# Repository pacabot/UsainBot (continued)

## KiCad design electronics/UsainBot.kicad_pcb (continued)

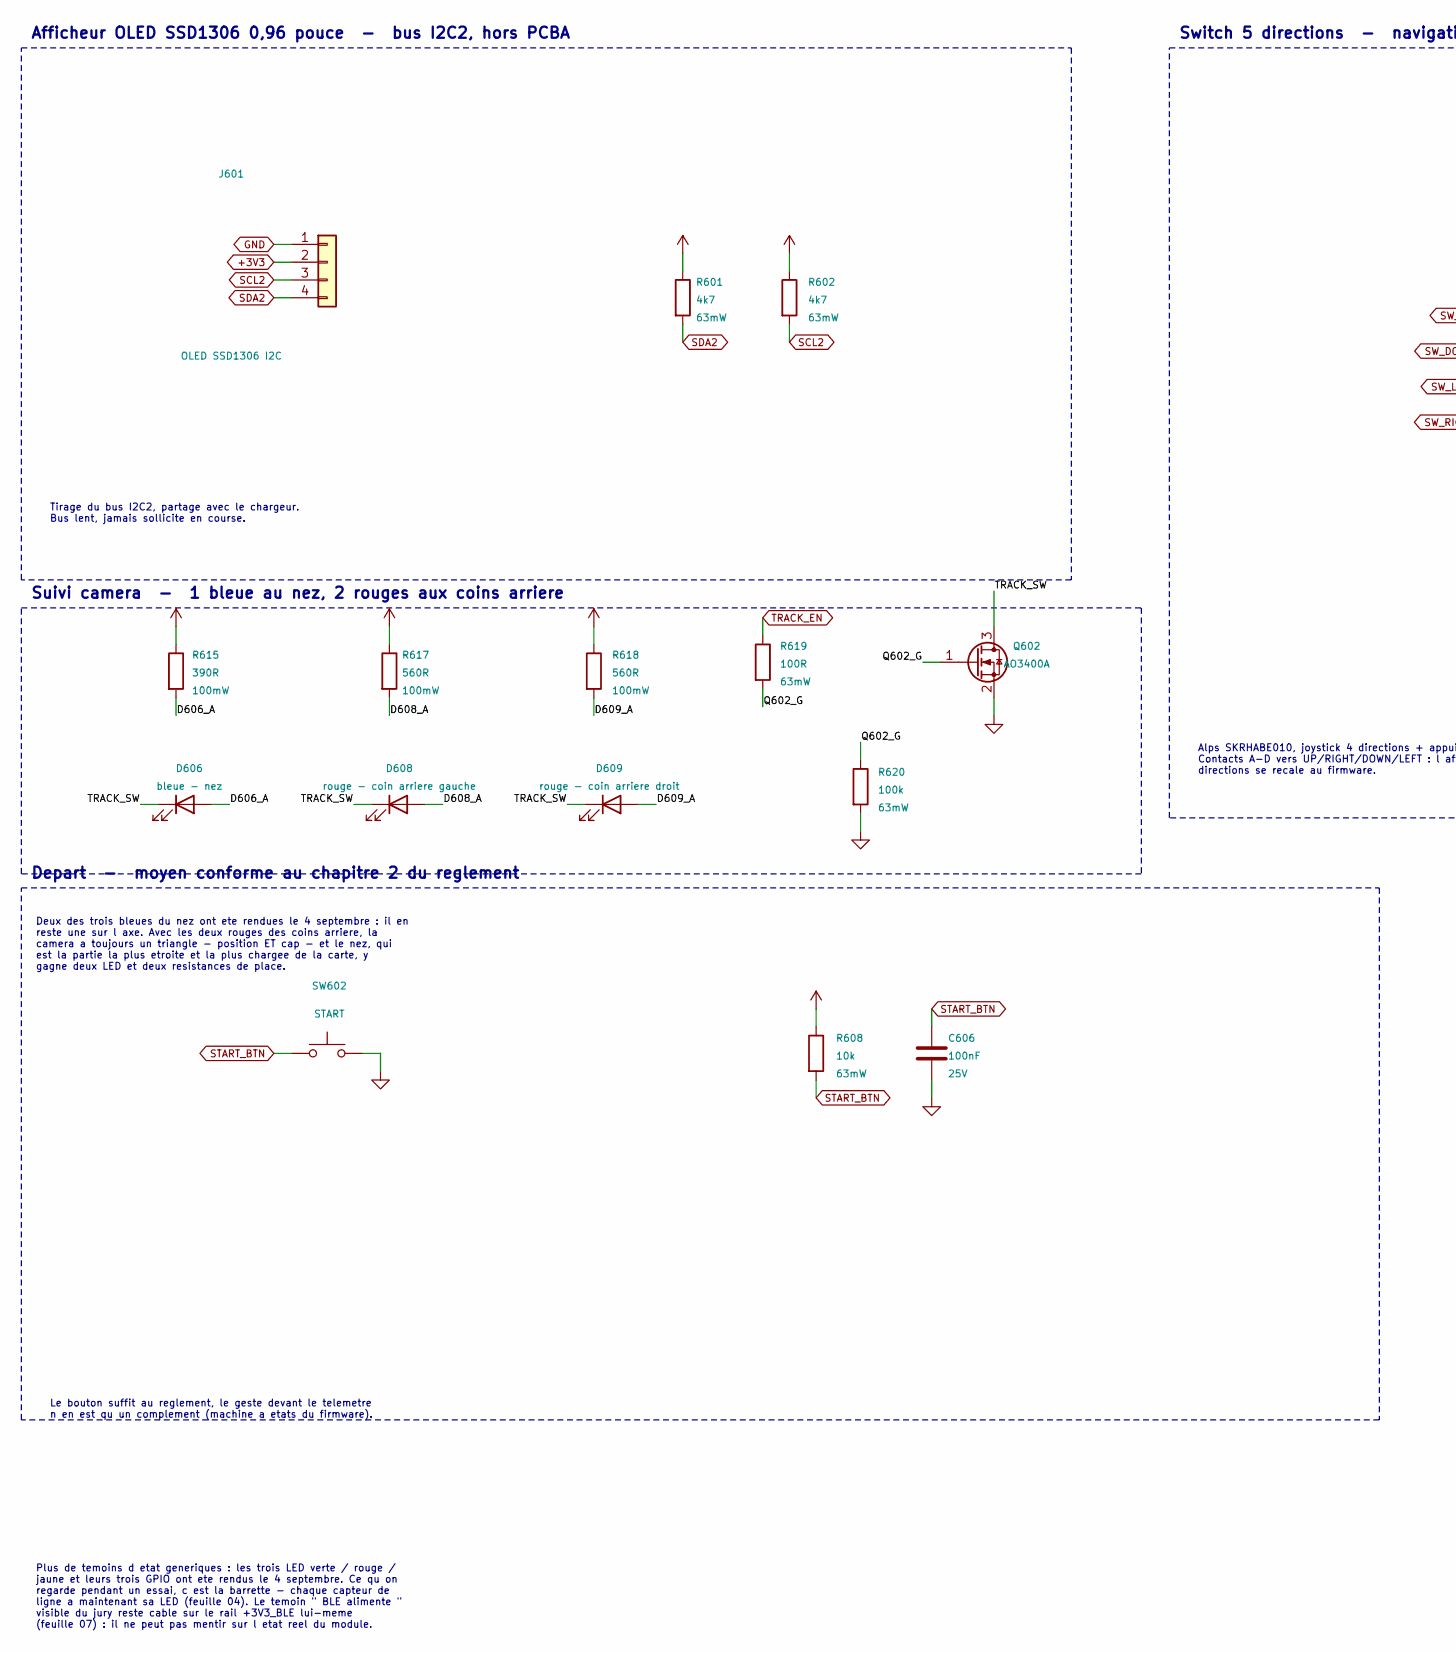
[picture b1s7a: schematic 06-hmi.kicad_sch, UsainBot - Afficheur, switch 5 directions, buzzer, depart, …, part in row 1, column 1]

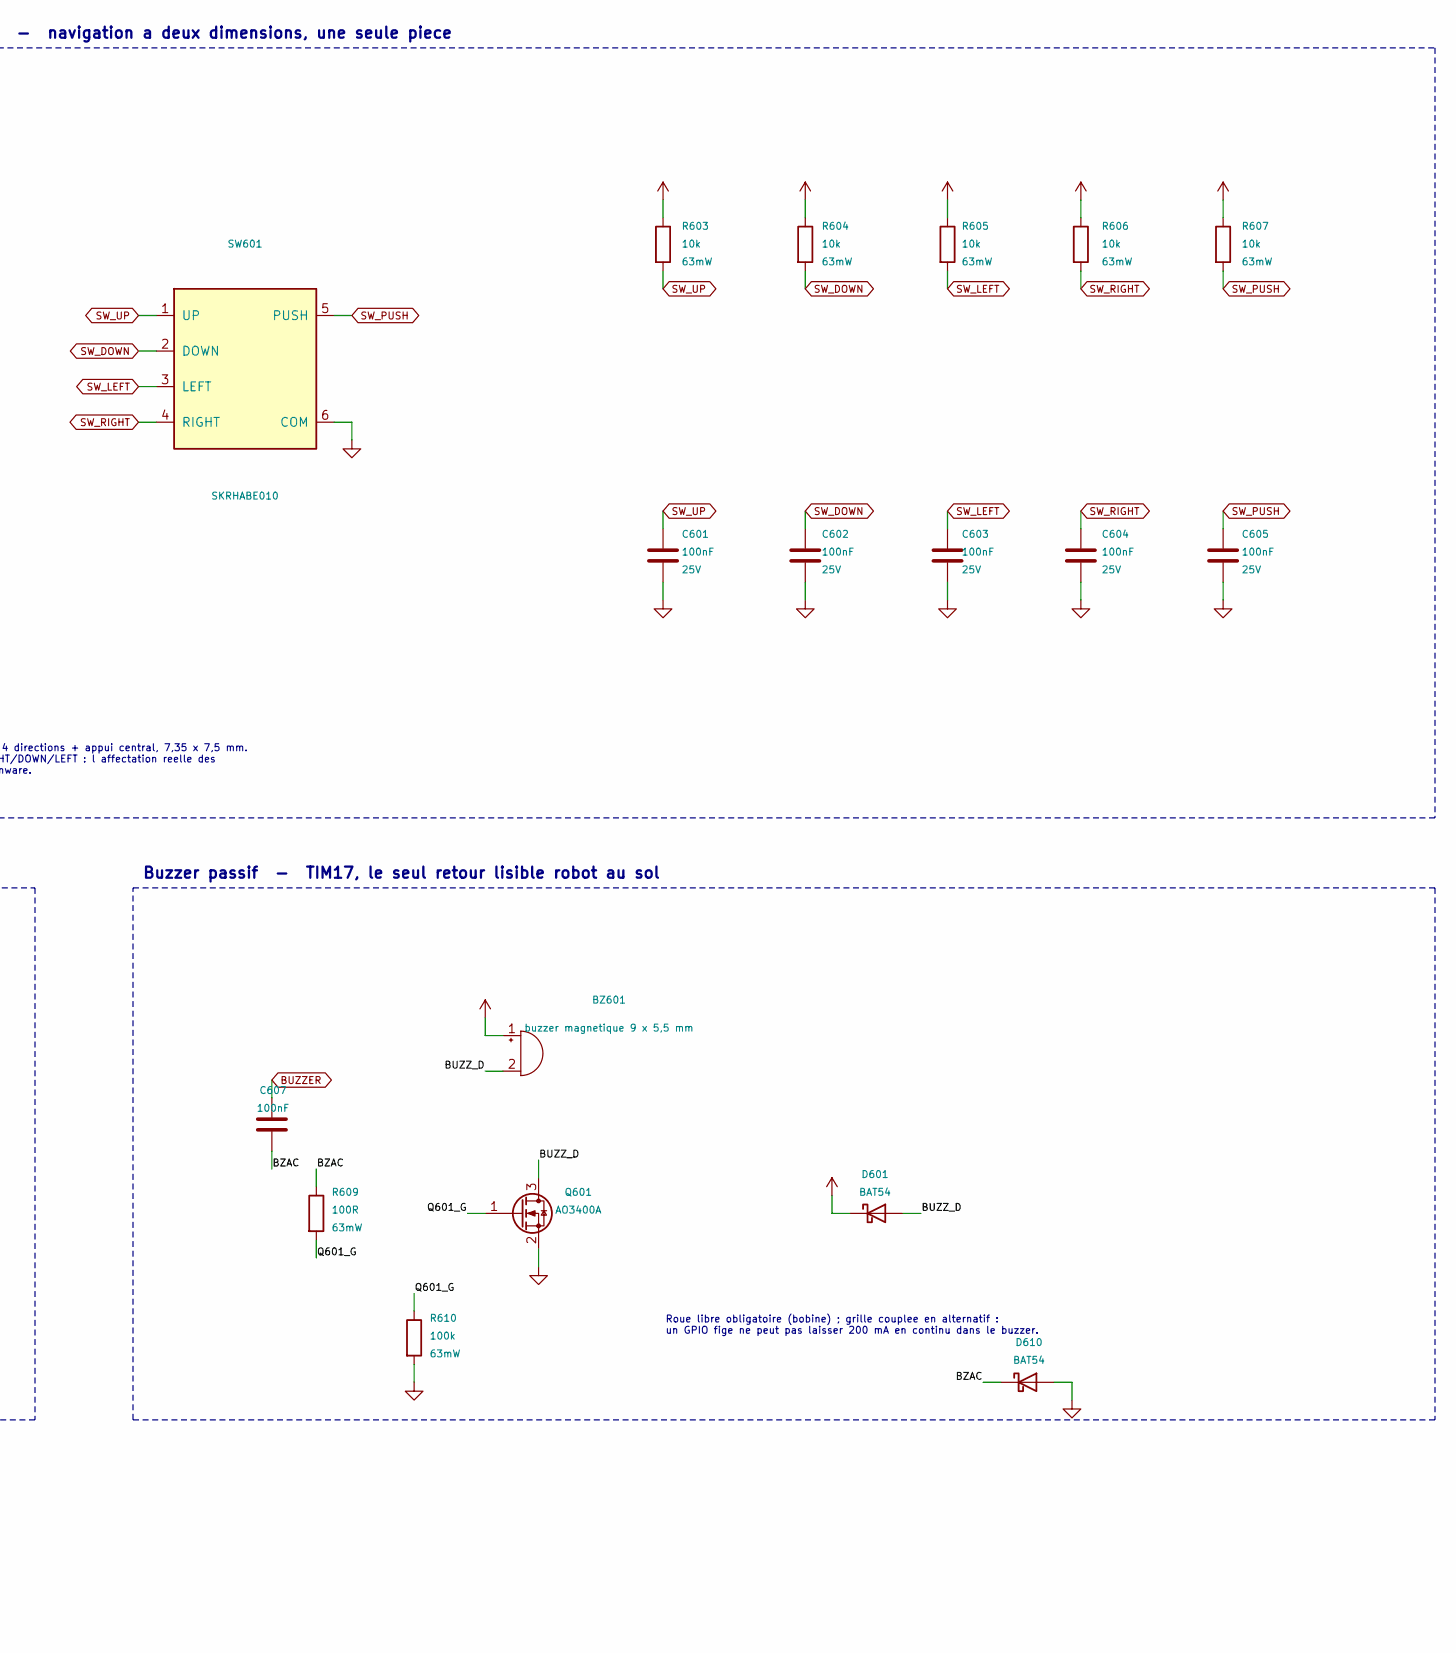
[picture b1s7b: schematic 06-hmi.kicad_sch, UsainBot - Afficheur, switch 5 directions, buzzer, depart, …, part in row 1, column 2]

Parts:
BZ601: buzzer magnetique 9 x 5,5 mm; MagneticBuzzer_ProSignal_ABI-009-RC
C601, C602, C603, C604, C605, C606: 100nF; C_0402_1005Metric; Voltage 25V
C607: 100nF; C_0402_1005Metric
D601, D610: BAT54; D_SOD-323
D606: bleue - nez; LED_0603_1608Metric
D608: rouge - coin arriere gauche; LED_0603_1608Metric
D609: rouge - coin arriere droit; LED_0603_1608Metric
J601: OLED SSD1306 I2C; OLED_096_I2C
Q601, Q602: AO3400A; SOT-23
R601, R602: 4k7; R_0402_1005Metric
R603, R604, R605, R606, R607, R608: 10k; R_0402_1005Metric
R609, R619: 100R; R_0402_1005Metric
R610, R620: 100k; R_0402_1005Metric
R615: 390R; R_0603_1608Metric
R617, R618: 560R; R_0603_1608Metric
SW601: SKRHABE010; LCSC C144855
SW602: START; SW_SPST_B3U-1000P

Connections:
/IHM/BUZZ_D: BZ601.2 (-), D601.2 (A), Q601.3 (D)
/IHM/BZAC: C607.2, D610.1 (K), R609.1
/IHM/D606_A: D606.2 (A), R615.2
/IHM/D608_A: D608.2 (A), R617.2
/IHM/D609_A: D609.2 (A), R618.2
/IHM/Q601_G: Q601.1 (G), R609.2, R610.1
/IHM/Q602_G: Q602.1 (G), R619.2, R620.1
/IHM/TRACK_SW: D606.1 (K), D608.1 (K), D609.1 (K), Q602.3 (D)
BUZZER: C607.1; also elsewhere on the board
SCL2: J601.3, R602.2; also elsewhere on the board
SDA2: J601.4, R601.2; also elsewhere on the board
START_BTN: C606.1, R608.2, SW602.1; also elsewhere on the board
SW_DOWN: C602.1, R604.2, SW601.2 (DOWN); also elsewhere on the board
SW_LEFT: C603.1, R605.2, SW601.3 (LEFT); also elsewhere on the board
SW_PUSH: C605.1, R607.2, SW601.5 (PUSH); also elsewhere on the board
SW_RIGHT: C604.1, R606.2, SW601.4 (RIGHT); also elsewhere on the board
SW_UP: C601.1, R603.2, SW601.1 (UP); also elsewhere on the board
TRACK_EN: R619.1; also elsewhere on the board

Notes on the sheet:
Plus de temoins d etat generiques : les trois LED verte / rouge / jaune et leurs trois GPIO ont ete rendus le 4 septembre. Ce qu on regarde pendant un essai, c est la barrette - chaque capteur de ligne a maintenant sa LED (feuille 04). Le temoin " BLE alimente " visible du jury reste cable sur le r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
Deux des trois bleues du nez ont ete rendues le 4 septembre : il en reste une sur l axe. Avec les deux rouges des coins arriere, la camera a toujours un triangle - position ET cap - et le nez, qui est la partie la plus etroite et la plus chargee de la carte, y gagne deux LED et deux resistances de 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
Le bouton suffit au reglement, le geste devant le telemetre n en est qu un complement (machine a etats du firmware).
Tirage du bus I2C2, partage avec le chargeur. Bus lent, jamais sollicite en course.
Switch 5 directions - navigation a deux dimensions, une seule piece
Buzzer passif - TIM17, le seul retour lisible robot au sol
Suivi camera - 1 bleue au nez, 2 rouges aux coins arriere
Roue libre obligatoire (bobine) ; grille couplee en alternatif : un GPIO fige ne peut pas laisser 200 mA en continu dans le buzzer.
Depart - moyen conforme au chapitre 2 du reglement
Afficheur OLED SSD1306 0,96 pouce - bus I2C2, hors PCBA
Alps SKRHABE010, joystick 4 directions + appui central, 7,35 x 7,5 mm. Contacts A-D vers UP/RIGHT/DOWN/LEFT : l affectation reelle des directions se recale au firmware.

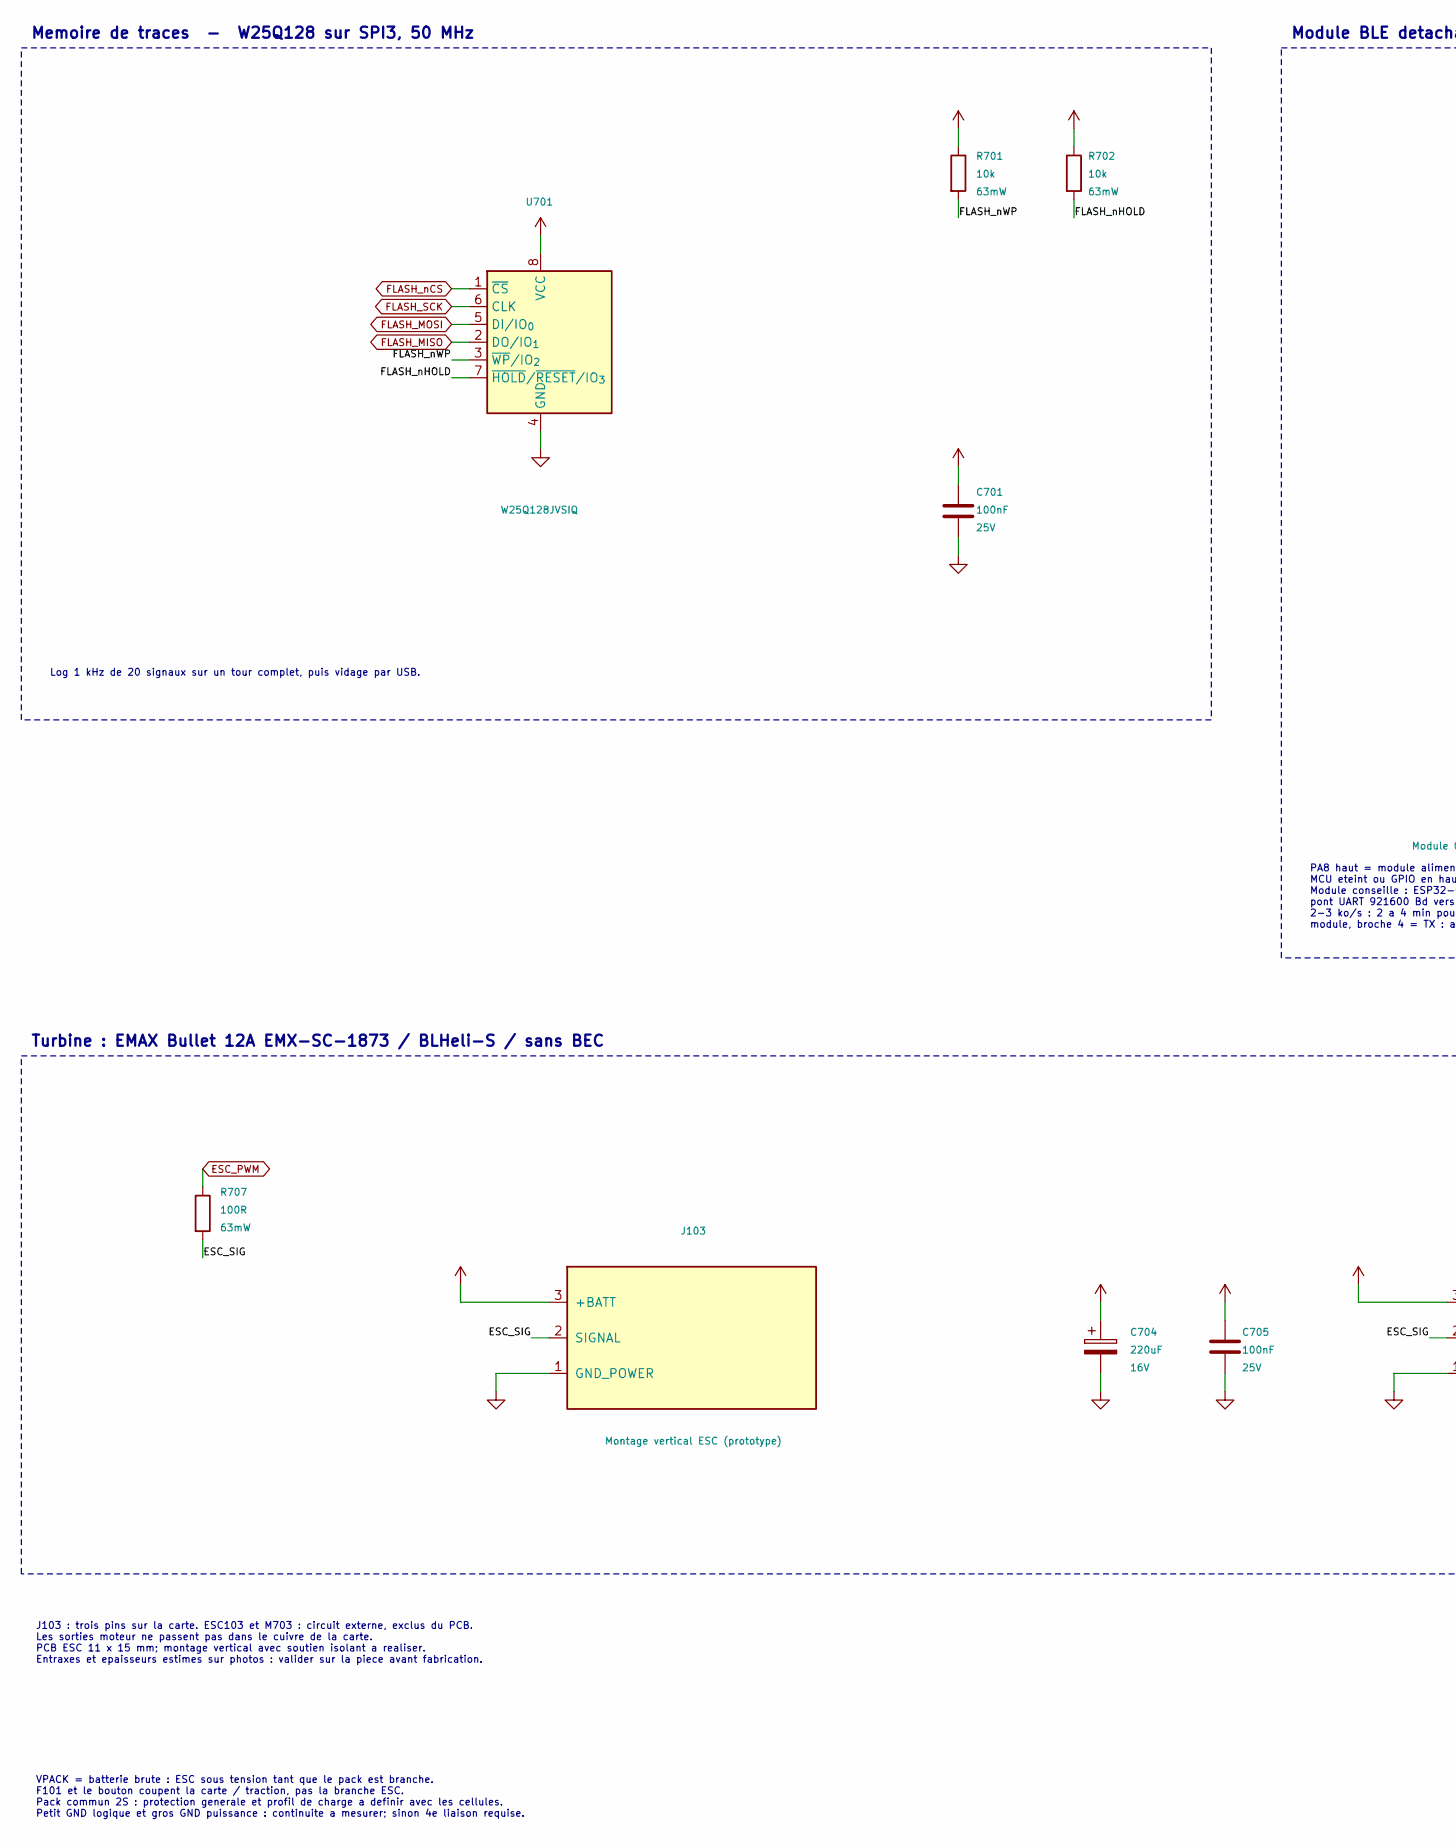
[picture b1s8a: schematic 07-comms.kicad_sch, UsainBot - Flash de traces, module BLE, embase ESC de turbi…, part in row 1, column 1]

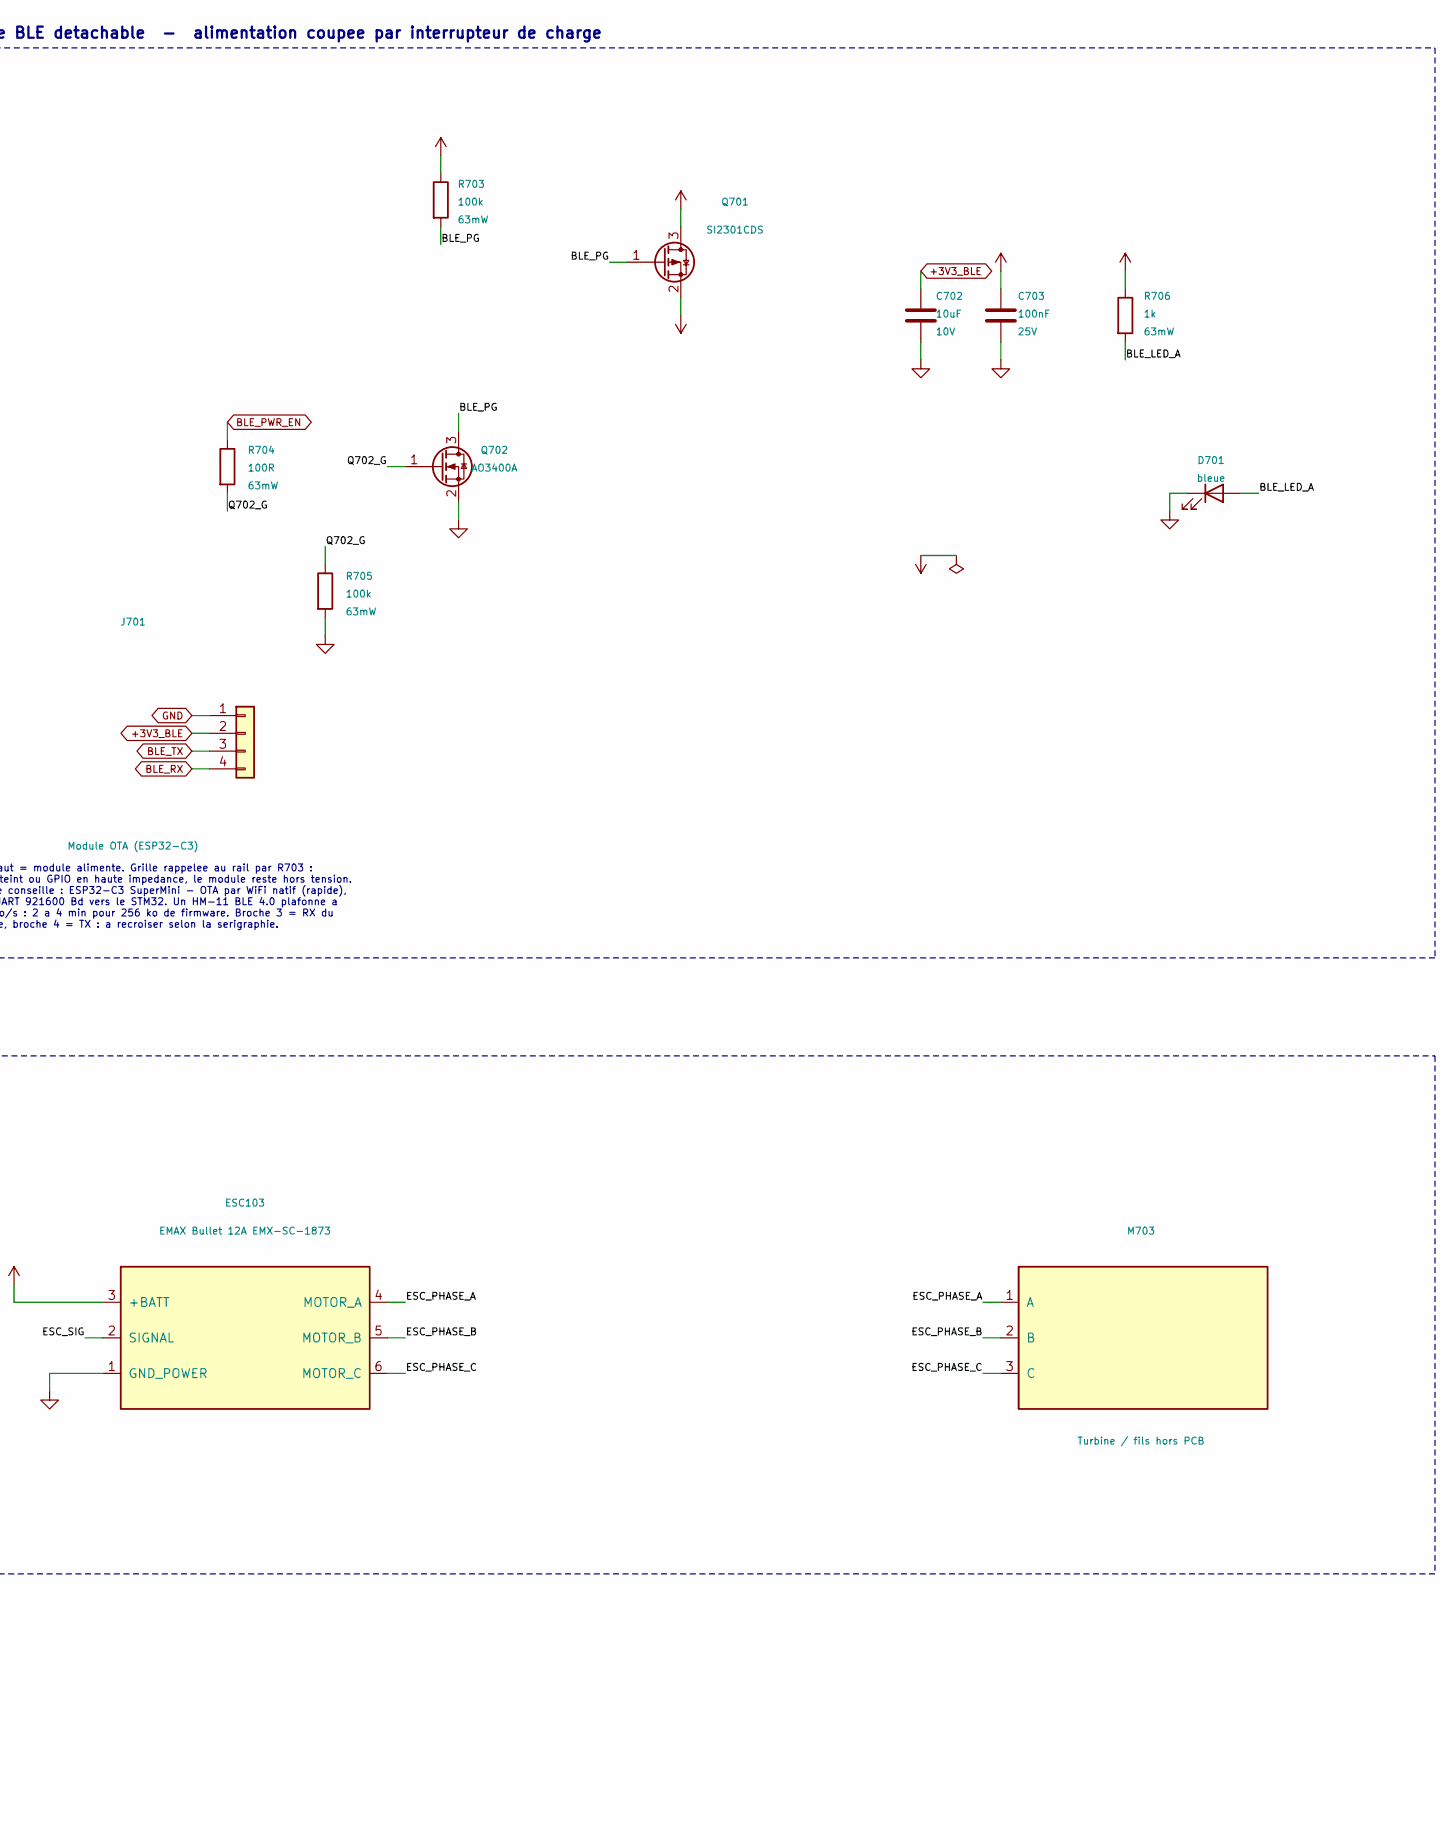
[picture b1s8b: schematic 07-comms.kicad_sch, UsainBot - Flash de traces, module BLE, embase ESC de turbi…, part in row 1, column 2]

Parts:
C701, C703, C705: 100nF; C_0402_1005Metric; Voltage 25V
C702: 10uF; C_0805_2012Metric; Voltage 10V
C704: 220uF; CP_Elec_6.3x7.7; Voltage 16V
D701: bleue; LED_0603_1608Metric
ESC103: EMAX Bullet 12A EMX-SC-1873; EMAX_Bullet_12A_Vertical_3Pin_PROTOTYPE; MPN EMX-SC-1873
J103: Montage vertical ESC (prototype); EMAX_Bullet_12A_Vertical_3Pin_PROTOTYPE
J701: Module OTA (ESP32-C3); PinHeader_1x04_P2.54mm_Vertical
M703: Turbine / fils hors PCB
Q701: SI2301CDS; SOT-23
Q702: AO3400A; SOT-23
R701, R702: 10k; R_0402_1005Metric
R703, R705: 100k; R_0402_1005Metric
R704, R707: 100R; R_0402_1005Metric
R706: 1k; R_0402_1005Metric
U701: W25Q128JVSIQ; SOIC-8_5.3x5.3mm_P1.27mm

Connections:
+3V3_BLE: C702.1, C703.1, J701.2, Q701.3 (D), R706.1
/Traces et turbine/BLE_LED_A: D701.2 (A), R706.2
/Traces et turbine/BLE_PG: Q701.1 (G), Q702.3 (D), R703.2
/Traces et turbine/ESC_SIG: ESC103.2 (SIGNAL), J103.2 (SIGNAL), R707.2
/Traces et turbine/FLASH_nHOLD: R702.2, U701.7 (~HOLD/~RESET/IO_{3})
/Traces et turbine/FLASH_nWP: R701.2, U701.3 (~WP/IO_{2})
/Traces et turbine/Q702_G: Q702.1 (G), R704.2, R705.1
BLE_PWR_EN: R704.1; also elsewhere on the board
BLE_RX: J701.4; also elsewhere on the board
BLE_TX: J701.3; also elsewhere on the board
ESC_PWM: R707.1; also elsewhere on the board
FLASH_MISO: U701.2 (DO/IO_{1}); also elsewhere on the board
FLASH_MOSI: U701.5 (DI/IO_{0}); also elsewhere on the board
FLASH_SCK: U701.6 (CLK); also elsewhere on the board
FLASH_nCS: U701.1 (~CS); also elsewhere on the board
unnamed: ESC103.4 (MOTOR_A), M703.1 (A)
unnamed: ESC103.5 (MOTOR_B), M703.2 (B)
unnamed: ESC103.6 (MOTOR_C), M703.3 (C)
VPACK: C704.1, C705.1, ESC103.3 (+BATT), J103.3 (+BATT); also elsewhere on the board

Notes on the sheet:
Memoire de traces - W25Q128 sur SPI3, 50 MHz
Turbine : EMAX Bullet 12A EMX-SC-1873 / BLHeli-S / sans BEC
Log 1 kHz de 20 signaux sur un tour complet, puis vidage par USB.
PA8 haut = module alimente. Grille rappelee au rail par R703 : MCU eteint ou GPIO en haute impedance, le module reste hors tension. Module conseille : ESP32-C3 SuperMini - OTA par WiFi natif (rapide), pont UART 921600 Bd vers le STM32. Un HM-11 BLE 4.0 plafonne a 2-3 ko/s : 2 a 4 min pour 256 ko de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
VPACK = batterie brute : ESC sous tension tant que le pack est branche. F101 et le bouton coupent la carte / traction, pas la branche ESC. Pack commun 2S : protection generale et profil de charge a definir avec les cellules. Petit GND logique et gros GND puissance : continuite a mesurer; sinon 4e l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
J103 : trois pins sur la carte. ESC103 et M703 : circuit externe, exclus du PCB. Les sorties moteur ne passent pas dans le cuivre de la carte. PCB ESC 11 x 15 mm; montage vertical avec soutien isolant a realiser. Entraxes et epaisseurs estimes sur photos : valider sur la piece avant fabrication.
Module BLE detachable - alimentation coupee par interrupteur de charge

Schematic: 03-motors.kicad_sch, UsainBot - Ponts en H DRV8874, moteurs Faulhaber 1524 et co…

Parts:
C301, C303, C305, C351, C353, C355: 100nF; C_0402_1005Metric; Voltage 25V
C302, C308, C309, C352, C358, C359: 1nF; C_0402_1005Metric; Voltage 25V
C304, C354: 100uF; CP_EIA-7343-20_Kemet-V; Voltage 16V poly
C306, C356: 22nF; C_0402_1005Metric; Voltage 25V
C307, C357: 100nF; C_0805_2012Metric; Voltage 50V
C310: 1uF; C_0402_1005Metric; Voltage 25V; LCSC C52923
C311: 4.7uF; C_0603_1608Metric; Voltage 16V; LCSC C19666
J301, J351: Moteur Faulhaber + IE2; TE_Micro-MaTch_215079-6_2x03_P1.27mm_Vertical; MPN TE 7-215079-6
R301, R304, R306, R354, R356: 10k; R_0402_1005Metric
R302: 6k8; R_0402_1005Metric
R303, R353: 100k; R_0402_1005Metric
R305, R355: 20k; R_0402_1005Metric
R307, R357: 1k; R_0402_1005Metric
R308, R309, R310, R358, R359, R360: 100R; R_0402_1005Metric
U301, U351: DRV8874PWPR; HTSSOP-16-1EP_4.4x5mm_P0.65mm_EP3.4x5mm; LCSC C1855818
U302: TPS70950DBVR; SOT-23-5; LCSC C96028

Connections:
/Moteurs/CPH_L: C306.1, U301.13 (CPH)
/Moteurs/CPH_R: C356.1, U351.13 (CPH)
/Moteurs/CPL_L: C306.2, U301.14 (CPL)
/Moteurs/CPL_R: C356.2, U351.14 (CPL)
/Moteurs/ENC_5V: C311.1, J301.4 (VDD), J351.4 (VDD), U302.5 (OUT)
/Moteurs/ENC_L_A_RAW: J301.6 (A), R309.1
/Moteurs/ENC_L_B_RAW: J301.5 (B), R310.1
/Moteurs/ENC_R_A_RAW: J351.6 (A), R359.1
/Moteurs/ENC_R_B_RAW: J351.5 (B), R360.1
/Moteurs/IMODE_L: R305.1, U301.7 (IMODE)
/Moteurs/IMODE_R: R355.1, U351.7 (IMODE)
/Moteurs/IPROPI_L_RAW: R307.1, R308.1, U301.6 (IPROPI)
/Moteurs/IPROPI_R_RAW: R357.1, R358.1, U351.6 (IPROPI)
/Moteurs/MOT_L_OUT1: C307.1, J301.2 (M+), U301.8 (OUT1)
/Moteurs/MOT_L_OUT2: C307.2, J301.1 (M-), U301.10 (OUT2)
/Moteurs/MOT_R_OUT1: C357.1, J351.2 (M+), U351.8 (OUT1)
/Moteurs/MOT_R_OUT2: C357.2, J351.1 (M-), U351.10 (OUT2)
/Moteurs/PMODE_L: R306.2, U301.16 (PMODE)
/Moteurs/PMODE_R: R356.2, U351.16 (PMODE)
/Moteurs/VCP_L: C305.1, U301.12 (VCP)
/Moteurs/VCP_R: C355.1, U351.12 (VCP)
/Moteurs/VREF_MOT: C301.1, C351.1, R301.2, R302.1, U301.5 (VREF), U351.5 (VREF)
ENC_L_A: C308.1, R309.2; also elsewhere on the board
ENC_L_B: C309.1, R310.2; also elsewhere on the board
ENC_R_A: C358.1, R359.2; also elsewhere on the board
ENC_R_B: C359.1, R360.2; also elsewhere on the board
IPROPI_L: C302.1, R308.2; also elsewhere on the board
IPROPI_R: C352.1, R358.2; also elsewhere on the board
MOT_L_IN1: U301.1 (EN/IN1); also elsewhere on the board
MOT_L_IN2: U301.2 (PH/IN2); also elsewhere on the board
MOT_L_nFAULT: R304.2, U301.4 (~nFAULT); also elsewhere on the board
MOT_L_nSLEEP: R303.1, U301.3 (nSLEEP); also elsewhere on the board
MOT_R_IN1: U351.1 (EN/IN1); also elsewhere on the board
MOT_R_IN2: U351.2 (PH/IN2); also elsewhere on the board
MOT_R_nFAULT: R354.2, U351.4 (~nFAULT); also elsewhere on the board
MOT_R_nSLEEP: R353.1, U351.3 (nSLEEP); also elsewhere on the board

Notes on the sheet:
Codeurs IE2 : 4,5-5,5 V (Faulhaber). EN sur +3V3 : le 5 V n'apparaît qu'avec le MCU, dont PB4/PB5/PC6/PC7 (FT_h) ne tolèrent 5 V qu'alimentés. 26 mA max, chute <= 0,26 V.
Nappe Faulhaber sur Micro-MaTch 215079-6 : impairs a gauche, fil rouge = M+. Fils moteur torsades, 100 nF aux bornes.
Reference de limitation de courant, commune aux deux ponts
C301 au pied de U301.5 ; C351 au pied de U351.5. Le rail commun de seuil est filtre localement aux deux ponts.
Moteur droit - pont complet, 6 A crete, retour de courant
VREF_MOT = 3,3 x 6,8/16,8 = 1,34 V. ITRIP = VREF / (AIPROPI x RIPROPI) = 1,34 / (450 uA/A x 1 k) ~ 3,0 A, soit environ deux fois le courant de calage du GM12-N20 a 6 V. Le seuil se change en retouchant R302 seule.
Moteur gauche - pont complet, 6 A crete, retour de courant

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
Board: 4 copper layers, 343 parts (12 on the bottom side), 224 nets, no tracks yet.

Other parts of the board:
M1, M2: Faulhaber 1524T006SR + IE2 + 15/10; Motor_Faulhaber_1524_15-10
M3: Turbine_EDF27_dessus

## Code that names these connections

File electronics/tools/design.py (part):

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                  fp='Package_TO_SOT_SMD:SOT-23-6', ref_at=(128, 30), val_at=(128, 60))
    cx(sh, u1.pin('1'), 'USB_DP_C');  cx(sh, u1.pin('6'), '$USB_DP')
    cx(sh, u1.pin('3'), 'USB_DM_C');  cx(sh, u1.pin('4'), '$USB_DM')
    cx(sh, u1.pin('5'), 'VBUS_IN');   cx(sh, u1.pin('2'), '@GND')
    sh.note('Les paires 1/6 et 3/4 sont reliees en interne :\nle signal traverse le boitier.', 100, 68, 1.0)

    # ---------------------------------------------------------- chargeur
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                  fp='Package_DFN_QFN:HVQFN-24-1EP_4x4mm_P0.5mm_EP2.6x2.6mm_ThermalVias',
                  fields={'LCSC': 'C2761614'}, ref_at=(150, 106), val_at=(150, 180))
    cx_bar(sh, u2, ('19', '20', '25'), '@GND')
    cx(sh, u2.pin('23'), 'VBUS_IN')                       # VBUS
    cx_bar(sh, u2, ('21', '22'), 'PMID')
    cx_bar(sh, u2, ('17', '18'), 'SW_CHG')
    cx_bar(sh, u2, ('15', '16'), 'SNS_CHG')
    cx_bar(sh, u2, ('13', '14'), '@VPACK')
    cx(sh, u2.pin('12'), 'BTST')
    cx(sh, u2.pin('11'), 'REGN')
    cx(sh, u2.pin('9'),  'MID_R')                          # via 300 ohm
    cx(sh, u2.pin('10'), 'CBSET_R')                        # via R de bilan
    cx(sh, u2.pin('8'),  'ILIM')
    cx(sh, u2.pin('7'),  'TS')
    cx(sh, u2.pin('24'), '$GND')                           # PSEL bas = adaptateur
    cx(sh, u2.pin('4'),  '$SDA2')
    cx(sh, u2.pin('5'),  '$SCL2')
    cx(sh, u2.pin('6'),  '$CHG_INT')
    cx(sh, u2.pin('3'),  'CD')
    cx(sh, u2.pin('2'),  'CHG_STAT')
    cx(sh, u2.pin('1'),  'CHG_PG')

    # etage de puissance du chargeur
    C(sh, 'C101', '1uF/25V', 106, 92, 'VBUS_IN', '@GND', C06)
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    sw1 = sh.place('Switch:SW_Push', 'SW101', 'MARCHE / ARRET', 232, 102,
                   fp='Button_Switch_SMD:SW_SPST_B3U-1000P',
                   ref_at=(232, 94), val_at=(232, 98))
    cx(sh, sw1.pin('1'), 'BTN_N')
    cx(sh, sw1.pin('2'), '@GND')
    horiz(sh, 'Device:D_Schottky', 'D106', 'BAT54', 272, 102, 'PWR_G', 'BTN_N',
          'Diode_SMD:D_SOD-323')
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                      ref_at=(qx, 44), val_at=(qx, 48))
        cx_bar(sh, q_, ('1', '2', '3'), 'VBAT_SW_IN')     # source cote pack
        cx_bar(sh, q_, ('5', '6', '7', '8'), '@VBAT')     # drain cote charge
        cx(sh, q_.pin('4'), 'PWR_G')
    R(sh, 'R114', '100k', 340, 80, 'PWR_G', 'VBAT_SW_IN')
    sh.note('Pack commun : MR30 3 contacts GND / MID / VPACK.\n'
            'MID apporte le point milieu au BQ25887. Coupure par\n'
            'deux canaux P en parallele (Rds/2), grille rappelee a la source\n'
            'par R114 : coupe par defaut, aucune fuite de grille.\n'
            'MISE SOUS TENSION PAR BOUTON POUSSOIR. L appui tire la grille au\n'
            '0 V par D106 et les FET conduisent. Le firmware met PE0 a 1 des le\n'
            'demarrage : Q104 tient la grille, le bouton peut etre relache. Il\n'
            'lit ensuite le bouton sur PE1 (diviseur 470k/220k, 0,319 x VPACK) et coupe\n'
            'en relachant PE0 - apres avoir ferme la flash,\n'
            'ce qu un interrupteur ne savait pas faire. C123 donne 100 ms de\n'
            'retombee : un reset du MCU ne coupe pas l alimentation.\n'
            'A l arret : courant carte de veille; ESC reste alimente sur VPACK.', 296, 245, 1.0)
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                  ref_at=(290, 158), val_at=(290, 162))
    cx(sh, u3.pin('VIN'), '@VBAT')
    cx(sh, u3.pin('GND'), '@GND')
    cx(sh, u3.pin('SW'),  'SW_BUCK')
    cx(sh, u3.pin('BST'), 'BST_BUCK')
    cx(sh, u3.pin('FB'),  'FB_BUCK')
    cx(sh, u3.pin('RT'),  'RT_BUCK')
    cx(sh, u3.pin('SS'),  'SS_BUCK')
    cx(sh, u3.pin('EN'),  'EN_BUCK')
    C(sh, 'C111', '10uF/25V', 232, 156, '@VBAT', '@GND', C1210)
    C(sh, 'C112', '10uF/25V', 244, 156, '@VBAT', '@GND', C1210)
    C(sh, 'C113', '100nF', 258, 156, '@VBAT', '@GND', C06)
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    R(sh, 'R119', '22k', 32, 190, '@VBAT', '$VBAT_SENSE')
    R(sh, 'R120', '10k', 32, 208, '$VBAT_SENSE', '@GND')
    C(sh, 'C121', '100nF', 54, 208, '$VBAT_SENSE', '@GND', C06)
    sh.note('7,3 V -> 2,28 V, directement sur PC0. Le 74HC4051 qui multiplexait\n'
            'cette mesure avec les deux IPROPI a disparu avec le passage au\n'
            'LQFP144 : chacun des trois a desormais son entree, et surtout les\n'
            'deux courants moteur se lisent au meme instant (PF11 sur ADC1,\n'
            'PF13 sur ADC2, meme numero de voie). Thevenin 6,9 k, C121 sert de\n'
            'reservoir de charge pour l echantillonnage.',
            18, 232, 1.0)
    sh.note('VPACK est deja pilote par la broche BAT du chargeur :\n'
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# Brochage du STM32H723ZGT6 (LQFP144), donne PAR NOM DE PORT et non par
# numero de broche. C'est ce qui a rendu le passage du LQFP100 au LQFP144
# sur : 85 des 87 affectations se sont transposees telles quelles, parce
# qu'une affectation est un choix de PORT (PA0 porte la voie de ligne 00),
# jamais un choix de patte. Une table numerotee aurait demande de recopier
# 144 lignes a la main, et une erreur de brochage ne se voit pas a l'ERC.
# Les broches absentes de cette table sont declarees non connectees
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MCU_PORTS = {
    # --- service et horloge ------------------------------------------------
    'NRST': 'NRST',          'BOOT0': 'BOOT0',
    'PH0': 'OSC_IN',         'PH1': 'OSC_OUT',
    # --- alimentation et bouton --------------------------------------------
    'PE0': '$PWR_HOLD',      'PE1': '$PWR_BTN',
    # --- ponts moteur, codeurs ---------------------------------------------
    'PE9': '$MOT_L_IN1',     'PE11': '$MOT_L_IN2',
    'PE13': '$MOT_R_IN1',    'PE14': '$MOT_R_IN2',
    'PD0': '$MOT_L_nSLEEP',  'PD1': '$MOT_R_nSLEEP',
    'PD3': '$MOT_L_nFAULT',  'PD4': '$MOT_R_nFAULT',
    'PB4(NJTRST)': '$ENC_L_A', 'PB5': '$ENC_L_B',
    'PC6': '$ENC_R_A',       'PC7': '$ENC_R_B',
    # --- barrette de ligne : douze voies d ADC, une par capteur ------------
    'PA0': '$LINE_00', 'PA1': '$LINE_01', 'PA2': '$LINE_02', 'PA3': '$LINE_03',
    'PA4': '$LINE_04', 'PA5': '$LINE_05', 'PA6': '$LINE_06', 'PA7': '$LINE_07',
    'PB0': '$LINE_08', 'PB1': '$LINE_09', 'PC4': '$LINE_10', 'PC5': '$LINE_11',
    'PE7': '$IR_BANK_A',     'PE8': '$IR_BANK_B',
    # --- telemetrie : emission et trois voies de reception -----------------
    'PE2': '$TX_FL',         'PB2': '$TX_F',         'PC13': '$TX_L',
    'PC1': '$RX_F',          'PC2_C': '$RX_FL',      'PC3_C': '$RX_L',
    # --- surveillance analogique DIRECTE (le multiplexeur a disparu) -------
    # PF11 est ADC1_INP2 et PF13 ADC2_INP2 : meme numero de voie sur DEUX
    # convertisseurs, donc les deux courants moteur se lisent au meme
    # instant en mode double simultane. Le 74HC4051 l'interdisait par
    # construction - on lisait un moteur, on commutait, on attendait
    # l'etablissement, on lisait l'autre.
    'PF11': '$IPROPI_L',     'PF13': '$IPROPI_R',    'PC0': '$VBAT_SENSE',
    # --- inertie, flash, radio, USB ----------------------------------------
    'PE6': '$IMU_INT1',
    'PB12': '$IMU_nCS', 'PB13': '$IMU_SCK', 'PB14': '$IMU_MISO', 'PB15': '$IMU_MOSI',
    'PD2': '$FLASH_nCS',
    'PC10': '$FLASH_SCK', 'PC11': '$FLASH_MISO', 'PC12': '$FLASH_MOSI',
    'PA8': '$BLE_PWR_EN', 'PA9': '$BLE_TX', 'PA10': '$BLE_RX',
    'PA11': '$USB_DM', 'PA12': '$USB_DP',
    # --- IHM, turbine, chargeur, eclairage ---------------------------------
    'PE10': '$SW_UP', 'PE12': '$SW_DOWN', 'PE15': '$SW_LEFT',
    'PD10': '$SW_RIGHT', 'PD13': '$SW_PUSH', 'PD14': '$START_BTN',
    'PB10': '$SCL2', 'PB11': '$SDA2',
    'PB8': '$ESC_PWM', 'PB9': '$BUZZER',
    'PE3': '$CHG_CD_EN', 'PE4': '$CHG_INT', 'PE5': '$TRACK_EN',
    # --- debogage ----------------------------------------------------------
    'PA13(JTMS': 'SWDIO', 'PA14(JTCK': 'SWCLK', 'PB3(JTDO': 'SWO',
}
# broches d alimentation, traitees a part (VSS est empile sur une seule
# position dans le symbole : un seul raccordement les relie toutes)
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    y1 = sh.place('Device:Crystal_GND24_Small', 'Y201', '25 MHz / 10 ppm', 56, 130,
                  fp='Crystal:Crystal_SMD_3225-4Pin_3.2x2.5mm',
                  ref_at=(56, 122), val_at=(56, 140))
    cx(sh, y1.pin('1'), 'OSC_IN')
    cx(sh, y1.pin('3'), 'XTAL_OUT')
    cx_bar(sh, y1, ('2', '4'), '@GND', offset=5.08)
    C(sh, 'C215', '10pF', 28, 152, 'OSC_IN', '@GND')
    C(sh, 'C216', '10pF', 84, 152, 'XTAL_OUT', '@GND')
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        cx(sh, u.pin('2'),  f'$MOT_{tag}_IN2')
        cx(sh, u.pin('3'),  f'$MOT_{tag}_nSLEEP')
        cx(sh, u.pin('4'),  f'$MOT_{tag}_nFAULT')
        cx(sh, u.pin('5'),  'VREF_MOT')
        cx(sh, u.pin('6'),  f'IPROPI_{tag}_RAW')
        cx(sh, u.pin('7'),  f'IMODE_{tag}')
        cx(sh, u.pin('16'), f'PMODE_{tag}')
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                     fp='Package_SO:TSSOP-14_4.4x5mm_P0.65mm',
                     ref_at=(X + 66, Y + 72), val_at=(X + 66, Y + 94))
        cx(sh, t.pin('-'), f'PD_{tag}')
        cx(sh, t.pin('+'), 'VREF_RX')
        cx(sh, out_pin(t), f'TIA_{tag}')
        R(sh, f'R{n + 4}', '220k', X + 66, Y + 62, f'PD_{tag}', f'TIA_{tag}')
        C(sh, f'C{n + 1}', '22pF', X + 88, Y + 62, f'PD_{tag}', f'TIA_{tag}')
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    b = sh.place('Amplifier_Operational:TLV9064', 'U501', 'TLV9064', 262, 236, unit=4,
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
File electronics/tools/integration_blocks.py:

"""Reviewed schematic blocks for the common 2S pack and external Bullet ESC.

The ESC module has six electrical ports but only three land on this PCB.
J103 is its three-pin mounting interface; ESC103 and M703 are off-board
electrical symbols. This preserves a real three-pad footprint without fake
motor copper on the motherboard. The module is counted once in the BOM.
"""
from pathlib import Path
import sexp
from kigen import q, fmt

ESC_FP = 'Pacabot:EMAX_Bullet_12A_Vertical_3Pin_PROTOTYPE'
ESC_URL = 'https://emax-usa.com/products/d-shot-bullet-series-12a-esc-blheli-s'

def prop(k, v, x=0, y=0, hidden=True):
    effects = ['effects', ['font', ['size', '1.27', '1.27']]]
    if hidden:
        effects.append(['hide', 'yes'])
    return ['property', q(k), q(v), ['at', fmt(x), fmt(y), '0'], effects]

def pin(number, name, x, y, angle, kind='passive'):
    return ['pin', kind, 'line', ['at', fmt(x), fmt(y), str(angle)],
            ['length', '2.54'],
            ['name', q(name), ['effects', ['font', ['size', '1.27', '1.27']]]],
            ['number', q(number), ['effects', ['font', ['size', '1.27', '1.27']]]]]

def symbol(name, ref, pins, description, fp='', on_board=True):
    return ['symbol', q(name), ['pin_names', ['offset', '1.016']],
            ['exclude_from_sim', 'no'], ['in_bom', 'yes'],
            ['on_board', 'yes' if on_board else 'no'],
            prop('Reference', ref, -12.7, 13.97, False),
            prop('Value', name, 0, -13.97, False), prop('Footprint', fp),
            prop('Datasheet', ESC_URL), prop('Description', description),
            ['symbol', q(name + '_0_1'),
             ['rectangle', ['start', '-17.78', '10.16'], ['end', '17.78', '-10.16'],
              ['stroke', ['width', '0.254'], ['type', 'default']],
              ['fill', ['type', 'background']]]],
            ['symbol', q(name + '_1_1')] + pins]

def ensure_symbols(library):
    root = sexp.parse(Path(library).read_text())[0]
    entries = [
        symbol('EMAX_Bullet_12A_EMX_SC_1873', 'ESC', [
            pin('1', 'GND_POWER', -20.32, -5.08, 0, 'power_in'),
            pin('2', 'SIGNAL', -20.32, 0, 0, 'input'),
            pin('3', '+BATT', -20.32, 5.08, 0, 'power_in'),
            pin('4', 'MOTOR_A', 20.32, 5.08, 180, 'output'),
            pin('5', 'MOTOR_B', 20.32, 0, 180, 'output'),
            pin('6', 'MOTOR_C', 20.32, -5.08, 180, 'output')],
            'Exact EMAX Bullet 12A BLHeli-S EMX-SC-1873; module outside motherboard. '
            'Input mounting via J103; phases wired directly to motor. Pin numbers are project mapping, '
            'not manufacturer numbering. Logic GND to power GND continuity must be measured.',
            ESC_FP, False),
        symbol('ESC_Vertical_Mount3', 'J', [
            pin('1', 'GND_POWER', -20.32, -5.08, 0),
            pin('2', 'SIGNAL', -20.32, 0, 0),
            pin('3', '+BATT', -20.32, 5.08, 0)],
            'Three motherboard holes for solid copper pins soldered to ESC input pads; '
            'prototype geometry estimated from photographs; insulating support required.', ESC_FP),
        symbol('Turbine_3Phase_Offboard', 'M', [
            pin('1', 'A', -20.32, 5.08, 0),
            pin('2', 'B', -20.32, 0, 0),
            pin('3', 'C', -20.32, -5.08, 0)],
            'Three phase turbine motor, wired directly to ESC; no motherboard pads.', '', False)
    ]
    names = {sexp.unq(s[1]) for s in entries}
    root[:] = [n for n in root if not (isinstance(n, list) and n[0] == 'symbol' and sexp.unq(n[1]) in names)]
    root.extend(entries)
    Path(library).write_text(sexp.dump(root) + '\n')

def offboard(sh, ref):
    for item in sh.items:
        if not isinstance(item, list) or item[0] != 'symbol':
            continue
        props = {sexp.unq(p[1]): sexp.unq(p[2]) for p in sexp.find_all(item, 'property')}
        if props.get('Reference') == ref:
            sexp.find(item, 'on_board')[1] = 'no'

def build_esc(sh, api):
    cx, C, Rh = api['cx'], api['C'], api['Rh']
    sh.box(16, 168, 394, 74, 'Turbine : EMAX Bullet 12A EMX-SC-1873 / BLHeli-S / sans BEC')
    Rh(sh, 'R707', '100R', 42, 190, '$ESC_PWM', 'ESC_SIG')
    mount = sh.place('Pacabot:ESC_Vertical_Mount3', 'J103', 'Montage vertical ESC (prototype)',
                     112, 208, fp=ESC_FP, in_bom=False,
                     ref_at=(112, 193), val_at=(112, 223),
                     fields={'Mechanical_status': 'PROTOTYPE - measure physical ESC before fabrication',
                             'Power_pins': 'Solid copper diameter 1.20 mm; holes 1.40 mm; pads 3.00 mm'})
    esc = sh.place('Pacabot:EMAX_Bullet_12A_EMX_SC_1873', 'ESC103', 'EMAX Bullet 12A EMX-SC-1873',
                   240, 208, fp=ESC_FP, datasheet=ESC_URL,
                   ref_at=(240, 189), val_at=(240, 193),
                   fields={'Manufacturer': 'EMAX', 'MPN': 'EMX-SC-1873',
                           'Motherboard_interface': 'J103; phases 4/5/6 are direct external wires',
                           'Ground_check': 'Confirm small logic GND continuity to large power GND before assembly'})
    for part in (mount, esc):
        cx(sh, part.pin('1'), '@GND', 7.62)
        cx(sh, part.pin('2'), 'ESC_SIG', 2.54)
        cx(sh, part.pin('3'), '@VPACK', 12.7)
    offboard(sh, 'ESC103')
    motor = sh.place('Pacabot:Turbine_3Phase_Offboard', 'M703', 'Turbine / fils hors PCB',
                     368, 208, in_bom=False, ref_at=(368, 193), val_at=(368, 223))
    offboard(sh, 'M703')
    for ep, mp, letter in [('4', '1', 'A'), ('5', '2', 'B'), ('6', '3', 'C')]:
        cx(sh, esc.pin(ep), 'ESC_PHASE_' + letter)
        cx(sh, motor.pin(mp), 'ESC_PHASE_' + letter)
    C(sh, 'C704', '220uF/16V', 170, 210, '@VPACK', '@GND', api['CPOL'])
    sh._need('Device:C_Polarized')
    for item in sh.items:
        if isinstance(item, list) and item[0] == 'symbol':
            props = {sexp.unq(p[1]): sexp.unq(p[2]) for p in sexp.find_all(item, 'property')}
            if props.get('Reference') == 'C704':
                sexp.find(item, 'lib_id')[1] = q('Device:C_Polarized')
    C(sh, 'C705', '100nF', 188, 210, '@VPACK', '@GND')
    sh.note('J103 : trois pins sur la carte. ESC103 et M703 : circuit externe, exclus du PCB.\n'
            'Les sorties moteur ne passent pas dans le cuivre de la carte.\n'
            'PCB ESC 11 x 15 mm; montage vertical avec soutien isolant a realiser.\n'
            'Entraxes et epaisseurs estimes sur photos : valider sur la piece avant fabrication.', 18, 255, 1.0)
    sh.note('VPACK = batterie brute : ESC sous tension tant que le pack est branche.\n'
            'F101 et le bouton coupent la carte / traction, pas la branche ESC.\n'
            'Pack commun 2S : protection generale et profil de charge a definir avec les cellules.\n'
            'Petit GND logique et gros GND puissance : continuite a mesurer; sinon 4e liaison requise.', 18, 277, 1.0)

def build_battery(sh, api, footprint):
    j = sh.place('Connector_Generic:Conn_01x03', 'J102', 'Pack 2S - AMASS MR30',
                  254, 46, fp=footprint, ref_at=(254, 33), val_at=(254, 61),
                  datasheet='https://lucidar.me/en/electronics/files/mr30pb-m.pdf',
                  fields={'Manufacturer': 'AMASS', 'MPN': 'MR30PB-M30.G.Y', 'Mating_connector': 'MR30-F.G.Y; optional cover 98023.PG', 'Harness': 'Project pinout: 1 GND / 2 PACK_MID / 3 VPACK; AWG16 power, AWG24 MID; 5cm power leads each assumed', 'Rated_current': '20 A per manufacturer at deltaT 85K with AWG16; thermal validation required at 15.5A continuous /18.5A peak', 'Mechanical_revision': 'AMASS MR30PB-M 2021V1: 11.9x5.3x10.4mm; 3mm tails; pitch3.50; drill1.80+0.20/0', 'Operating_budget': 'ESC 12A continuous /15A peak + 2 DC motors x1A + electronics provisional1.5A'})
    api['cx'](sh, j.pin('1'), '@GND', 7.62)
    api['cx'](sh, j.pin('2'), 'PACK_MID', 2.54)
    api['cx'](sh, j.pin('3'), '@VPACK', 15.24)
